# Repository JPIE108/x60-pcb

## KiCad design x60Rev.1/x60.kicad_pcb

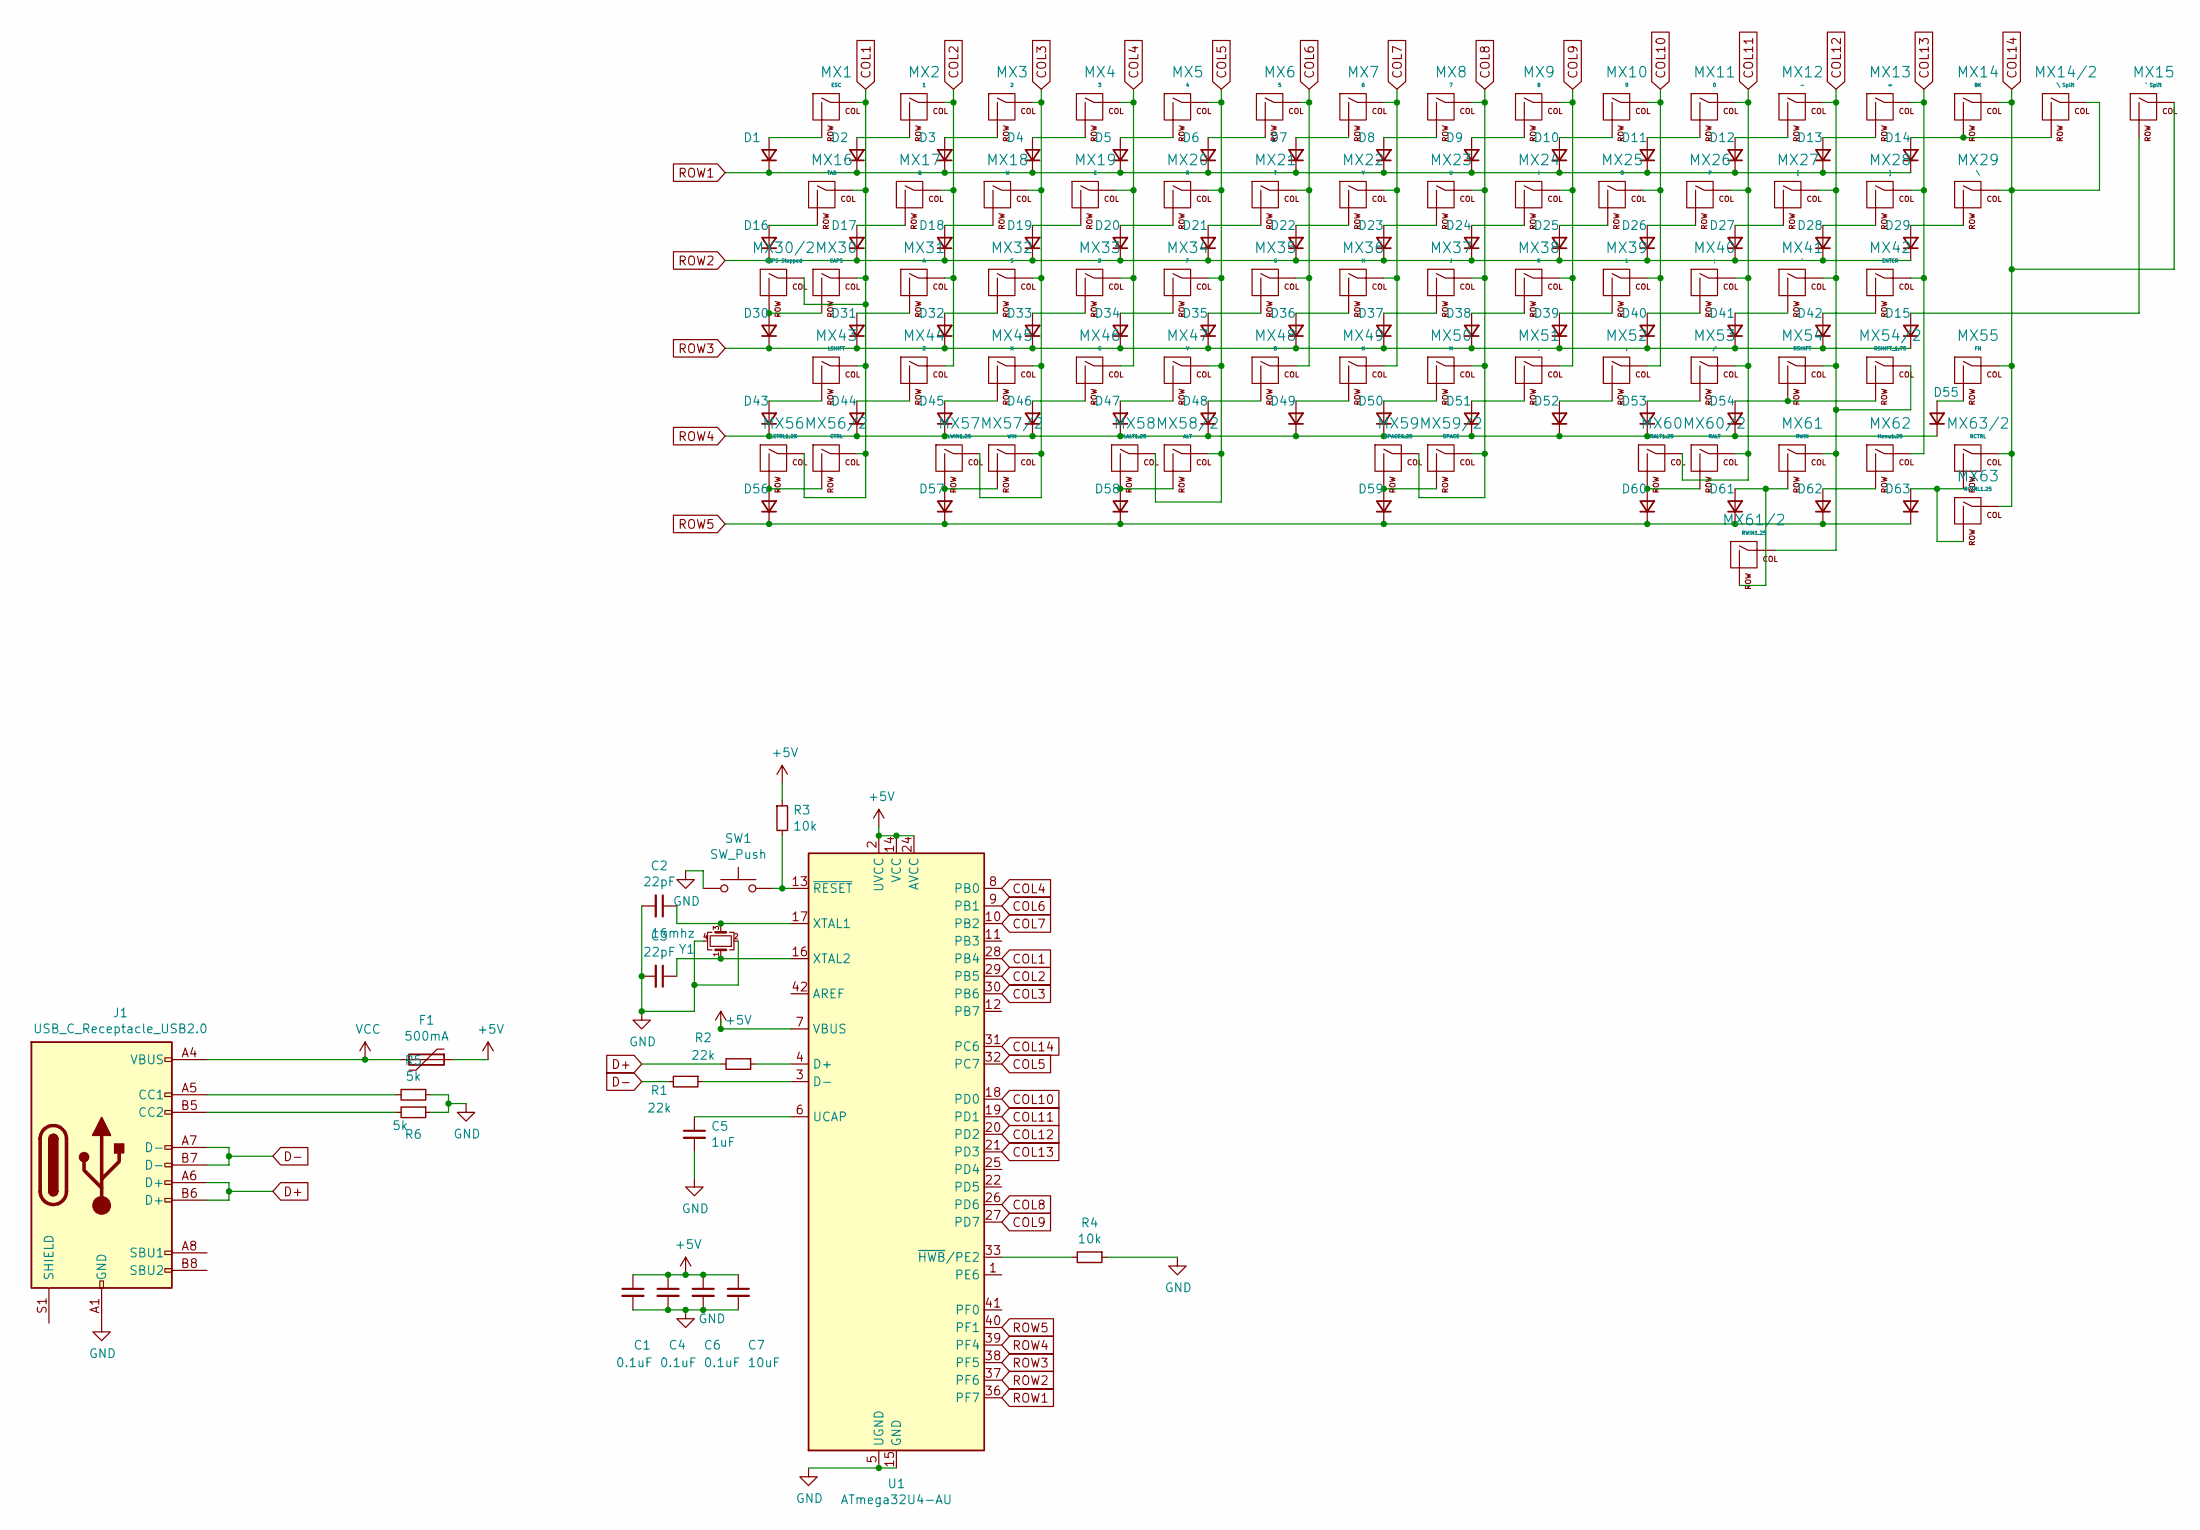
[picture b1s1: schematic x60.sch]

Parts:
C1, C4, C6: 0.1uF; C_0805_2012Metric
C2, C3: 22pF; C_0805_2012Metric
C5: 1uF; C_0805_2012Metric
C7: 10uF; C_0805_2012Metric
D1, D2, D3, D4, D5, D6, D7, D8, D9, D10, D11, D12, D13, D14, D15, D16, D17, D18, D19, D20, D21, D22, D23, D24, D25, D26, D27, D28, D29, D30, D31, D32, D33, D34, D35, D36, D37, D38, D39, D40, D41, D42, D43, D44, D45, D46, D47, D48, D49, D50, D51, D52, D53, D54, D55, D56, D57, D58, D59, D60, D61, D62, D63: D_Small; D_SOD-123
F1: 500mA; Fuse_1206_3216Metric
J1: USB_C_Receptacle_USB2.0; USB_C_Receptacle_HRO_TYPE-C-31-M-12
MX1: ESC; MXOnly-1U-NoLED
MX2: 1; MXOnly-1U-NoLED
MX3: 2; MXOnly-1U-NoLED
MX4: 3; MXOnly-1U-NoLED
MX5: 4; MXOnly-1U-NoLED
MX6: 5; MXOnly-1U-NoLED
MX7: 6; MXOnly-1U-NoLED
MX8: 7; MXOnly-1U-NoLED
MX9: 8; MXOnly-1U-NoLED
MX10: 9; MXOnly-1U-NoLED
MX11: 0; MXOnly-1U-NoLED
MX12: -; MXOnly-1U-NoLED
MX13: =; MXOnly-1U-NoLED
MX14: BK; MXOnly-2U-NoLED
MX14/2: \\ Split; MXOnly-1U-NoLED
MX15: ` Split; MXOnly-1U-NoLED
MX16: TAB; MXOnly-1.5U-NoLED
MX17: Q; MXOnly-1U-NoLED
MX18: W; MXOnly-1U-NoLED
MX19: E; MXOnly-1U-NoLED
MX20: R; MXOnly-1U-NoLED
MX21: T; MXOnly-1U-NoLED
MX22: Y; MXOnly-1U-NoLED
MX23: U; MXOnly-1U-NoLED
MX24: I; MXOnly-1U-NoLED
MX25: O; MXOnly-1U-NoLED
MX26: P; MXOnly-1U-NoLED
MX27: [; MXOnly-1U-NoLED
MX28: ]; MXOnly-1U-NoLED
MX29: \\; MXOnly-1.5U-NoLED
MX30: CAPS; MXOnly-1.75U-NoLED
MX30/2: CAPS Stepped; MXOnly-1.25U-NoLED
MX31: A; MXOnly-1U-NoLED
MX32: S; MXOnly-1U-NoLED
MX33: D; MXOnly-1U-NoLED
MX34: F; MXOnly-1U-NoLED
MX35: G; MXOnly-1U-NoLED
MX36: H; MXOnly-1U-NoLED
MX37: J; MXOnly-1U-NoLED
MX38: K; MXOnly-1U-NoLED
MX39: L; MXOnly-1U-NoLED
MX40: ;; MXOnly-1U-NoLED
MX41: '; MXOnly-1U-NoLED
MX42: ENTER; MXOnly-2.25U-NoLED
MX43: LSHIFT; MXOnly-2.25U-NoLED
MX44: Z; MXOnly-1U-NoLED
MX45: X; MXOnly-1U-NoLED
MX46: C; MXOnly-1U-NoLED
MX47: V; MXOnly-1U-NoLED
MX48: B; MXOnly-1U-NoLED
MX49: N; MXOnly-1U-NoLED
MX50: M; MXOnly-1U-NoLED
MX51: ,; MXOnly-1U-NoLED
MX52: .; MXOnly-1U-NoLED
MX53: /; MXOnly-1U-NoLED
MX54: RSHIFT; MXOnly-2.75U-NoLED
MX54/2: RSHIFT_1.75; MXOnly-1.75U-NoLED
MX55: FN; MXOnly-1U-NoLED
MX56: LCTRL1.25; MXOnly-1.25U-NoLED
MX56/2: CTRL; MXOnly-1.5U-NoLED
MX57: LWIN1.25; MXOnly-1.25U-NoLED
MX57/2: WIN; MXOnly-1U-NoLED
MX58: LALT1.25; MXOnly-1.25U-NoLED
MX58/2: ALT; MXOnly-1.5U-NoLED
MX59: SPACE6.25; MXOnly-6.25U-ReversedStabilizers-NoLED
MX59/2: SPACE; MXOnly-7U-ReversedStabilizers-NoLED
MX60: RALT1.25; MXOnly-1.25U-NoLED
MX60/2: RALT; MXOnly-1.5U-NoLED
MX61: RWIN; MXOnly-1U-NoLED
MX61/2: RWIN1.25; MXOnly-1.25U-NoLED
MX62: Menu1.25; MXOnly-1.25U-NoLED
MX63: RCTRL1.25; MXOnly-1.25U-NoLED
MX63/2: RCTRL; MXOnly-1.5U-NoLED
R1, R2: 22k; R_0805_2012Metric
R3, R4: 10k; R_0805_2012Metric
R5, R6: 5k; R_0805_2012Metric
SW1: SW_Push; SKQGADE010
U1: ATmega32U4-AU; TQFP-44_10x10mm_P0.8mm
Y1: 16mhz; Crystal_SMD_3225-4Pin_3.2x2.5mm

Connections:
+5V: C1.1, C4.1, C6.1, C7.1, F1.1, R3.1, U1.2 (UVCC), U1.7 (VBUS), U1.14 (VCC), U1.24 (AVCC), U1.34 (VCC), U1.44 (AVCC)
COL1: MX1.1 (COL), MX16.1 (COL), MX30.1 (COL), MX30/2.1 (COL), MX43.1 (COL), MX56.1 (COL), MX56/2.1 (COL), U1.28 (PB4)
COL2: MX2.1 (COL), MX17.1 (COL), MX31.1 (COL), MX44.1 (COL), U1.29 (PB5)
COL3: MX3.1 (COL), MX18.1 (COL), MX32.1 (COL), MX45.1 (COL), MX57.1 (COL), MX57/2.1 (COL), U1.30 (PB6)
COL4: MX4.1 (COL), MX19.1 (COL), MX33.1 (COL), MX46.1 (COL), U1.8 (PB0)
COL5: MX5.1 (COL), MX20.1 (COL), MX34.1 (COL), MX47.1 (COL), MX58.1 (COL), MX58/2.1 (COL), U1.32 (PC7)
COL6: MX6.1 (COL), MX21.1 (COL), MX35.1 (COL), MX48.1 (COL), U1.9 (PB1)
COL7: MX7.1 (COL), MX22.1 (COL), MX36.1 (COL), MX49.1 (COL), U1.10 (PB2)
COL8: MX8.1 (COL), MX23.1 (COL), MX37.1 (COL), MX50.1 (COL), MX59.1 (COL), MX59/2.1 (COL), U1.26 (PD6)
COL9: MX9.1 (COL), MX24.1 (COL), MX38.1 (COL), MX51.1 (COL), U1.27 (PD7)
COL10: MX10.1 (COL), MX25.1 (COL), MX39.1 (COL), MX52.1 (COL), U1.18 (PD0)
COL11: MX11.1 (COL), MX26.1 (COL), MX40.1 (COL), MX53.1 (COL), MX60.1 (COL), MX60/2.1 (COL), U1.19 (PD1)
COL12: MX12.1 (COL), MX27.1 (COL), MX41.1 (COL), MX54.1 (COL), MX54/2.1 (COL), MX61.1 (COL), MX61/2.1 (COL), U1.20 (PD2)
COL13: MX13.1 (COL), MX28.1 (COL), MX42.1 (COL), MX62.1 (COL), U1.21 (PD3)
COL14: MX14.1 (COL), MX14/2.1 (COL), MX15.1 (COL), MX29.1 (COL), MX55.1 (COL), MX63.1 (COL), MX63/2.1 (COL), U1.31 (PC6)
D+: J1.A6 (D+), J1.B6 (D+), R2.2
D-: J1.A7 (D-), J1.B7 (D-), R1.2
GND: C1.2, C2.2, C3.2, C4.2, C5.2, C6.2, C7.2, J1.A1 (GND), J1.A12 (GND), J1.B1 (GND), J1.B12 (GND), R4.1, R5.1, R6.1, SW1.1, U1.5 (UGND), U1.15 (GND), U1.23 (GND), U1.35 (GND), U1.43 (GND), Y1.2, Y1.4
unnamed: C2.1, U1.17 (XTAL1), Y1.3
unnamed: C3.1, U1.16 (XTAL2), Y1.1
unnamed: C5.1, U1.6 (UCAP)
unnamed: D1.2 (A), MX1.2 (ROW)
unnamed: D2.2 (A), MX2.2 (ROW)
unnamed: D3.2 (A), MX3.2 (ROW)
unnamed: D4.2 (A), MX4.2 (ROW)
unnamed: D5.2 (A), MX5.2 (ROW)
unnamed: D6.2 (A), MX6.2 (ROW)
unnamed: D7.2 (A), MX7.2 (ROW)
unnamed: D8.2 (A), MX8.2 (ROW)
unnamed: D9.2 (A), MX9.2 (ROW)
unnamed: D10.2 (A), MX10.2 (ROW)
unnamed: D11.2 (A), MX11.2 (ROW)
unnamed: D12.2 (A), MX12.2 (ROW)
unnamed: D13.2 (A), MX13.2 (ROW)
unnamed: D14.2 (A), MX14.2 (ROW), MX14/2.2 (ROW)
unnamed: D15.2 (A), MX15.2 (ROW)
unnamed: D16.2 (A), MX16.2 (ROW)
unnamed: D17.2 (A), MX17.2 (ROW)
unnamed: D18.2 (A), MX18.2 (ROW)
unnamed: D19.2 (A), MX19.2 (ROW)
unnamed: D20.2 (A), MX20.2 (ROW)
unnamed: D21.2 (A), MX21.2 (ROW)
unnamed: D22.2 (A), MX22.2 (ROW)
unnamed: D23.2 (A), MX23.2 (ROW)
unnamed: D24.2 (A), MX24.2 (ROW)
unnamed: D25.2 (A), MX25.2 (ROW)
unnamed: D26.2 (A), MX26.2 (ROW)
unnamed: D27.2 (A), MX27.2 (ROW)
unnamed: D28.2 (A), MX28.2 (ROW)
unnamed: D29.2 (A), MX29.2 (ROW)
unnamed: D30.2 (A), MX30.2 (ROW), MX30/2.2 (ROW)
unnamed: D31.2 (A), MX31.2 (ROW)
unnamed: D32.2 (A), MX32.2 (ROW)
unnamed: D33.2 (A), MX33.2 (ROW)
unnamed: D34.2 (A), MX34.2 (ROW)
unnamed: D35.2 (A), MX35.2 (ROW)
unnamed: D36.2 (A), MX36.2 (ROW)
unnamed: D37.2 (A), MX37.2 (ROW)
unnamed: D38.2 (A), MX38.2 (ROW)
unnamed: D39.2 (A), MX39.2 (ROW)
unnamed: D40.2 (A), MX40.2 (ROW)
unnamed: D41.2 (A), MX41.2 (ROW)
unnamed: D42.2 (A), MX42.2 (ROW)
unnamed: D43.2 (A), MX43.2 (ROW)
unnamed: D44.2 (A), MX44.2 (ROW)
unnamed: D45.2 (A), MX45.2 (ROW)
unnamed: D46.2 (A), MX46.2 (ROW)
unnamed: D47.2 (A), MX47.2 (ROW)
unnamed: D48.2 (A), MX48.2 (ROW)
unnamed: D49.2 (A), MX49.2 (ROW)
unnamed: D50.2 (A), MX50.2 (ROW)
unnamed: D51.2 (A), MX51.2 (ROW)
unnamed: D52.2 (A), MX52.2 (ROW)
unnamed: D53.2 (A), MX53.2 (ROW)
unnamed: D54.2 (A), MX54.2 (ROW), MX54/2.2 (ROW)
unnamed: D55.2 (A), MX55.2 (ROW)
unnamed: D56.2 (A), MX56.2 (ROW), MX56/2.2 (ROW)
unnamed: D57.2 (A), MX57.2 (ROW), MX57/2.2 (ROW)
unnamed: D58.2 (A), MX58.2 (ROW), MX58/2.2 (ROW)
unnamed: D59.2 (A), MX59.2 (ROW), MX59/2.2 (ROW)
unnamed: D60.2 (A), MX60.2 (ROW), MX60/2.2 (ROW)
unnamed: D61.2 (A), MX61.2 (ROW), MX61/2.2 (ROW)
unnamed: D62.2 (A), MX62.2 (ROW)
unnamed: D63.2 (A), MX63.2 (ROW), MX63/2.2 (ROW)
unnamed: J1.A5 (CC1), R5.2
unnamed: J1.B5 (CC2), R6.2
unnamed: R1.1, U1.3 (D-)
unnamed: R2.1, U1.4 (D+)
unnamed: R3.2, SW1.2, U1.13 (~RESET)
unnamed: R4.2, U1.33 (~HWB~/PE2)
ROW1: D1.1 (K), D2.1 (K), D3.1 (K), D4.1 (K), D5.1 (K), D6.1 (K), D7.1 (K), D8.1 (K), D9.1 (K), D10.1 (K), D11.1 (K), D12.1 (K), D13.1 (K), D14.1 (K), U1.36 (PF7)
ROW2: D16.1 (K), D17.1 (K), D18.1 (K), D19.1 (K), D20.1 (K), D21.1 (K), D22.1 (K), D23.1 (K), D24.1 (K), D25.1 (K), D26.1 (K), D27.1 (K), D28.1 (K), D29.1 (K), U1.37 (PF6)
ROW3: D15.1 (K), D30.1 (K), D31.1 (K), D32.1 (K), D33.1 (K), D34.1 (K), D35.1 (K), D36.1 (K), D37.1 (K), D38.1 (K), D39.1 (K), D40.1 (K), D41.1 (K), D42.1 (K), U1.38 (PF5)
ROW4: D43.1 (K), D44.1 (K), D45.1 (K), D46.1 (K), D47.1 (K), D48.1 (K), D49.1 (K), D50.1 (K), D51.1 (K), D52.1 (K), D53.1 (K), D54.1 (K), D55.1 (K), U1.39 (PF4)
ROW5: D56.1 (K), D57.1 (K), D58.1 (K), D59.1 (K), D60.1 (K), D61.1 (K), D62.1 (K), D63.1 (K), U1.40 (PF1)
VCC: F1.2, J1.A4 (VBUS), J1.A9 (VBUS), J1.B4 (VBUS), J1.B9 (VBUS)

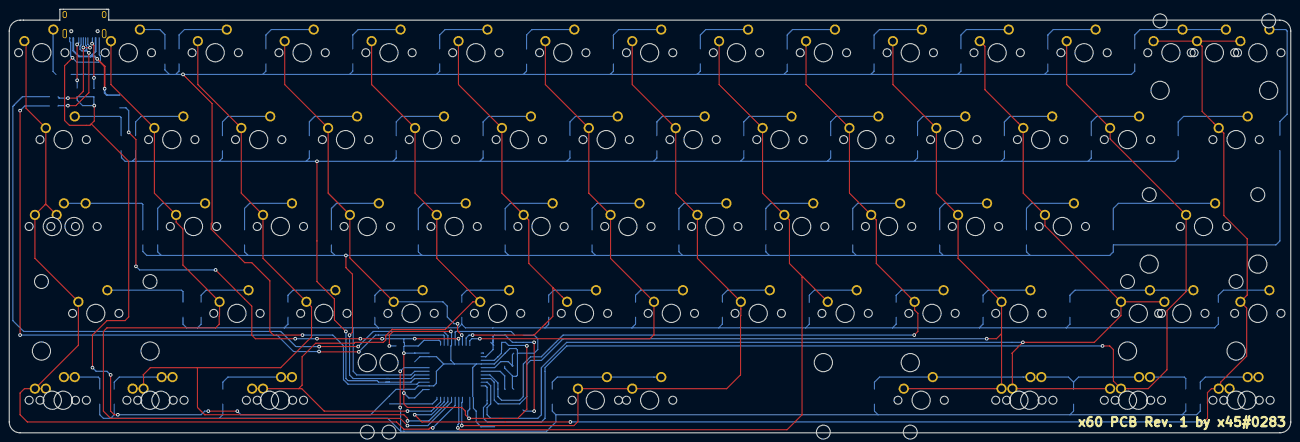
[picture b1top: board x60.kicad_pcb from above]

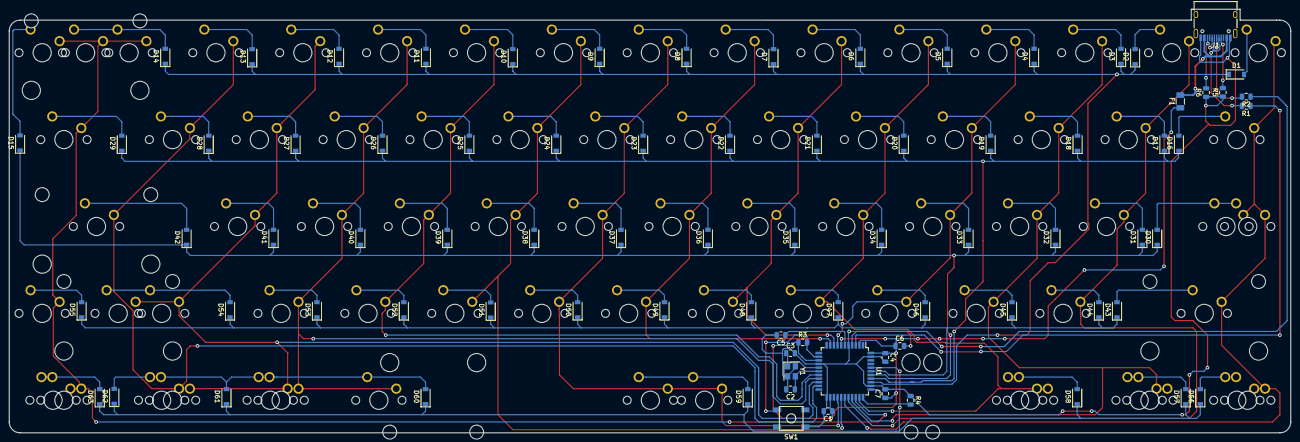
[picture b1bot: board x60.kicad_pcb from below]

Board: 2 copper layers, 281.0 x 92.9 mm, 154 parts (81 on the bottom side), 96 nets.

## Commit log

2021-10-30 Added Submodules
2021-10-30 Create sym-lib-table
2021-10-30 init
2021-10-30 wired mcu
2021-10-30 added switches
2021-10-30 updated wiring
2021-10-30 added support for split rs/bs
2021-10-30 applied footprints
2021-10-30 started designing pcb
2021-10-30 arranged the keys on the pcb
2021-10-30 added stepped caps
2021-10-30 added 1.25u bottom row support
2021-10-30 wired and arranged 1.25u bottom row
2021-10-30 adjusted diodes top row
2021-10-30 aligned diodes
2021-10-30 fixed diode arrangement
2021-10-30 placed mcu
2021-10-30 test
2021-10-30 fixed routing of mcu
2021-10-30 fixed mcu routing
2021-10-30 fixed capcitors being placed too close to the pcb
2021-10-30 wired all rows and columns
2021-10-30 connected rows to mcu
2021-10-31 wired all rows and columns to mcu
2021-10-31 flipped spacebar stabs
2021-10-31 rearranged lines after stabs flip
2021-10-31 adjusted some routing
2021-10-31 decoration
2021-10-31 added usb c to schematic
2021-10-31 updated schematic for usb
2021-10-31 redid usbc integration
2021-10-31 usb c port placement
2021-10-31 wired usb port
2021-10-31 generated gerbers
2021-10-31 generated production files
2021-10-31 organisation
2021-11-02 Completed First Revision
2021-11-05 updated components
2021-11-05 updated production
